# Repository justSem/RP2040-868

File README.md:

> `BE AWARE` This project is still in active development, I'm still in the process of ordering and testing prototypes, so the latest version is not tested to be fully-working as of yet.

# RP2040-868
A GPRS/GNSS/BTLE and LiPo/Li-ion charger integrated Pi Pico on credit-card format.

_Size: 99x50mm_

Title says it all!

This is a fully integrated RP2040-based board featuring the following:

* GPRS Enabled (with microSIM card format)
* GNSS (GPS, GLONASS, BEIDOU)
* BT(LE)
* Integrated LiPo/Li-ion charging circuit.
* USB-C (in USB2.0 mode) ports for future proofing.
* Programmable as if it's a "normal" RPI Pico
* Auto-switching power source: In case you connect both the Battery/USB Power and the USB-Program port, the device will automatically switch it's power source to the "PROG" port.

## The boards origin
Me and my friends work with GPS trackers a lot, for various purposes. For a while we used cheap AliExpress trackers, but we felt they couldn't be fully trusted. They're dirt-cheap but in return, closed-source.
We had absolutely no guarantee that it won't secretly send our data back to China.
So I decided to make our own version.

What started as a simple board grew out to be a fully-programmable board.
Since most of our group favor Python over C++ (simply because we're more used to Python :) ) we went with an RP2040

## Board Details
* The charger is a Monolithic Power [MP2624](https://www.monolithicpower.com/en/mp2624.html) 
* The GPRS/GNSS/BT(LE) Module is a SIMCom [SIM868](https://datasheet.lcsc.com/lcsc/1811011410_SIMCom-Wireless-Solutions-SIM868_C89549.pdf)
* At the heart of the board you'll find a Raspberry Pi [RP2040](https://datasheets.raspberrypi.com/rp2040/rp2040-datasheet.pdf)

## Quick Start
If you have the board you can simply access the programming mode by going through the following steps:
1. Connect a USB-C cable to the port labeled `PROG`
2. Press and hold the `RESET` button
3. Pres and hold the `PROG` button
4. Release the `RESET` button
5. Release the `PROG` button

The device should now present itself as removable storage to your system, allowing you to upload/download files to/from it.
You can use the provided code for some working examples.

## Costs
I haven't exactly calculated the costs. But for the 5 prototypes I built I spent roughly 30 euro's/board.
This includes overhead as some components had a minimium buy of 100 pieces.
So the exact costs are most likely below the number mentioned above.

# Planned Future
The plan is to make some changes in the future, these changes could be:

__Move to another Cellular Chip__

The SimCom chips can have 2A peak currents, which require a pcb designed to accomodate said currents.

__Support for more modern cellular acces__

GPRS is soon to be EOL. But at the time of writing there are no subsitutes which are worth the price in this project.
3G chips are available, but those networks are to be turned off 03-2022 in this country, which makes them not suitable for this project.
LTE-M (or other IoT bands) are still only available to commercial customers, chips for these networks are readily available but sadly not usable in this country.

For now it's waiting to see if any decent substitute will become available in the upcoming months.

__Support NanoSIM__

While it's theoretically possible with Rev 1.1 of the board, it hasn't been tested as of yet.

# F.A.Q.

__Do you sell these boards?__

No. I have no commercial interest with this project, but I might have spares at times, which I might be willing to send as long as you cover the costs.
Feel free to reach out if you're interested.

__Can you implement feature X?__

You're free to implement any software feature yourself. The boards are programmable for a reason :)

The board files can be altered using KiCad, enabling you to make hardware changes as well.

__I found a flaw__

Great! Please open an [issue](/issues/new/choose) and describe what you found.

# DISCLAIMER
I am in no way a professional PCB designer - this design could be flawed without me being aware of it.
I make things as a hobby without any guarantee on functionality, compatibility or reliability.
As stated in the [License](LICENSE.md) this product comes without any guarantee.

# CHANGELOG
### Rev 3.1
* Reversed change in crystal due to availability issues.
* Swapped SOIC-8 Flash for WSON variant.
* Removed SIM from `PROG` power-stage - no suitable DC-DC converter available for a reasonable price to do 5V->4V @ 2A.
* In order to access the SIM868 whilst programming, it is now required to either connect a battery, or an USB-cable to the `CHARGE` power-stage.

### Rev 2.0
* Swapped 100nF caps for 0402 to get them closer to the MCU.
* Moved around power-stage parts for thermal performance.
* Re-implemented USB connections to comply with USB Spec (impedance issues).

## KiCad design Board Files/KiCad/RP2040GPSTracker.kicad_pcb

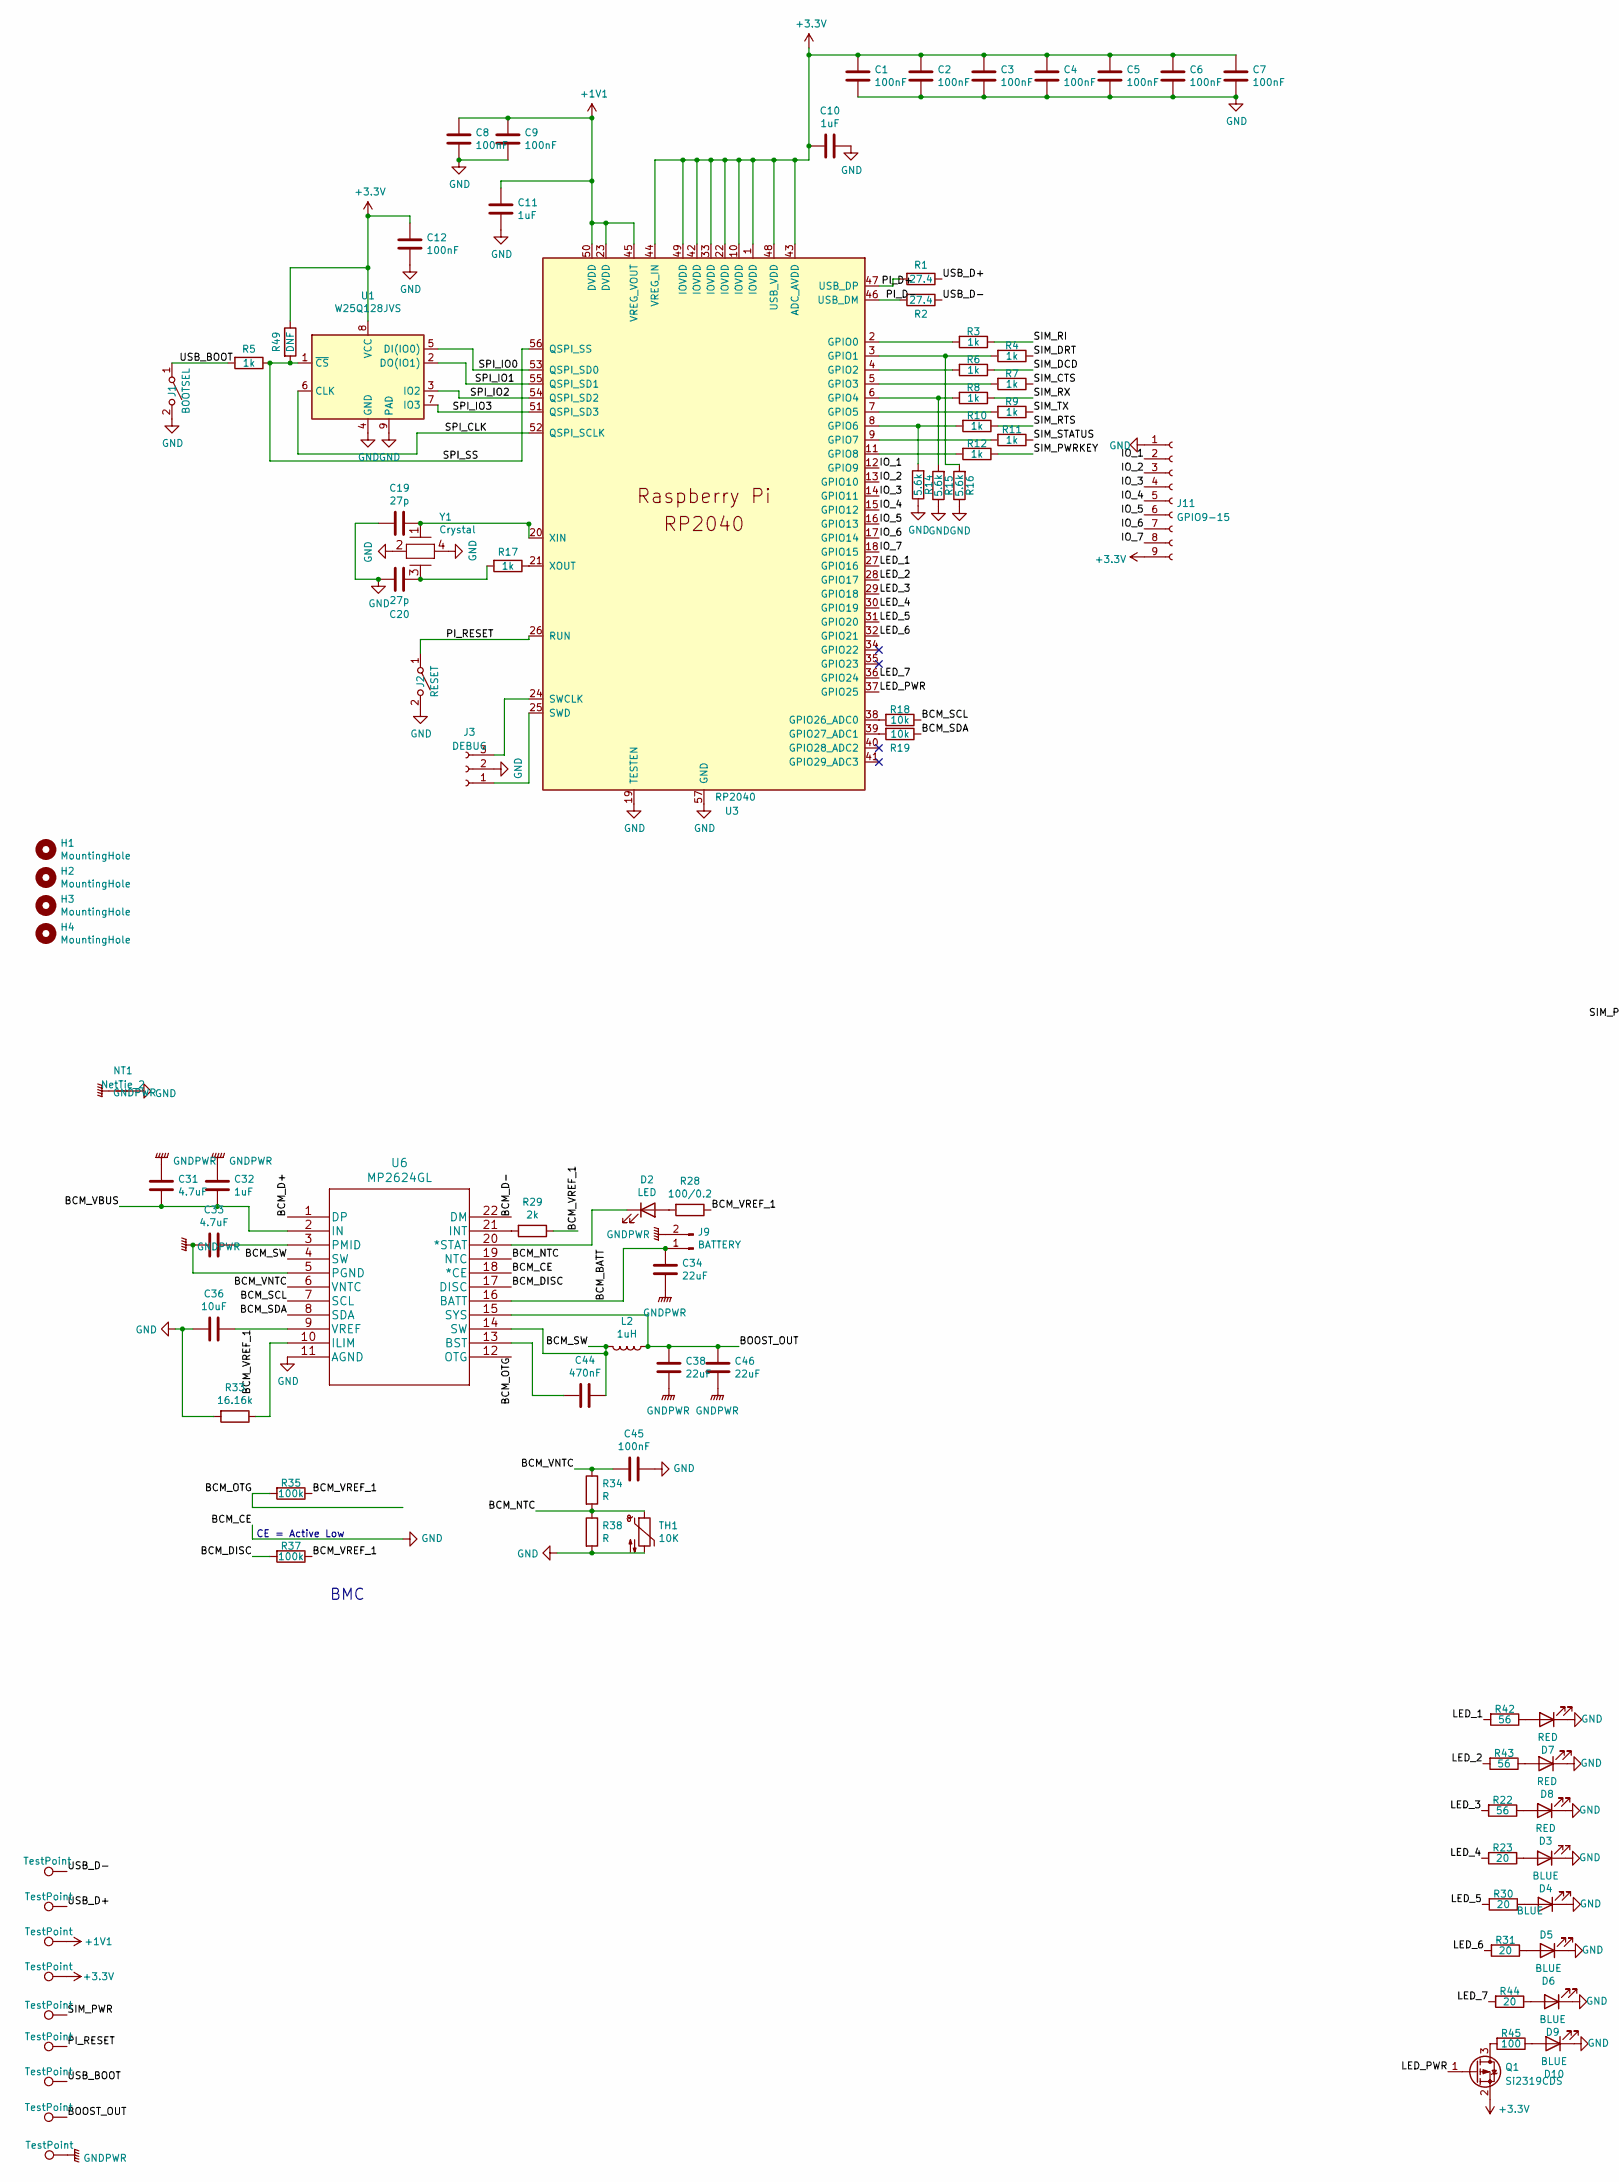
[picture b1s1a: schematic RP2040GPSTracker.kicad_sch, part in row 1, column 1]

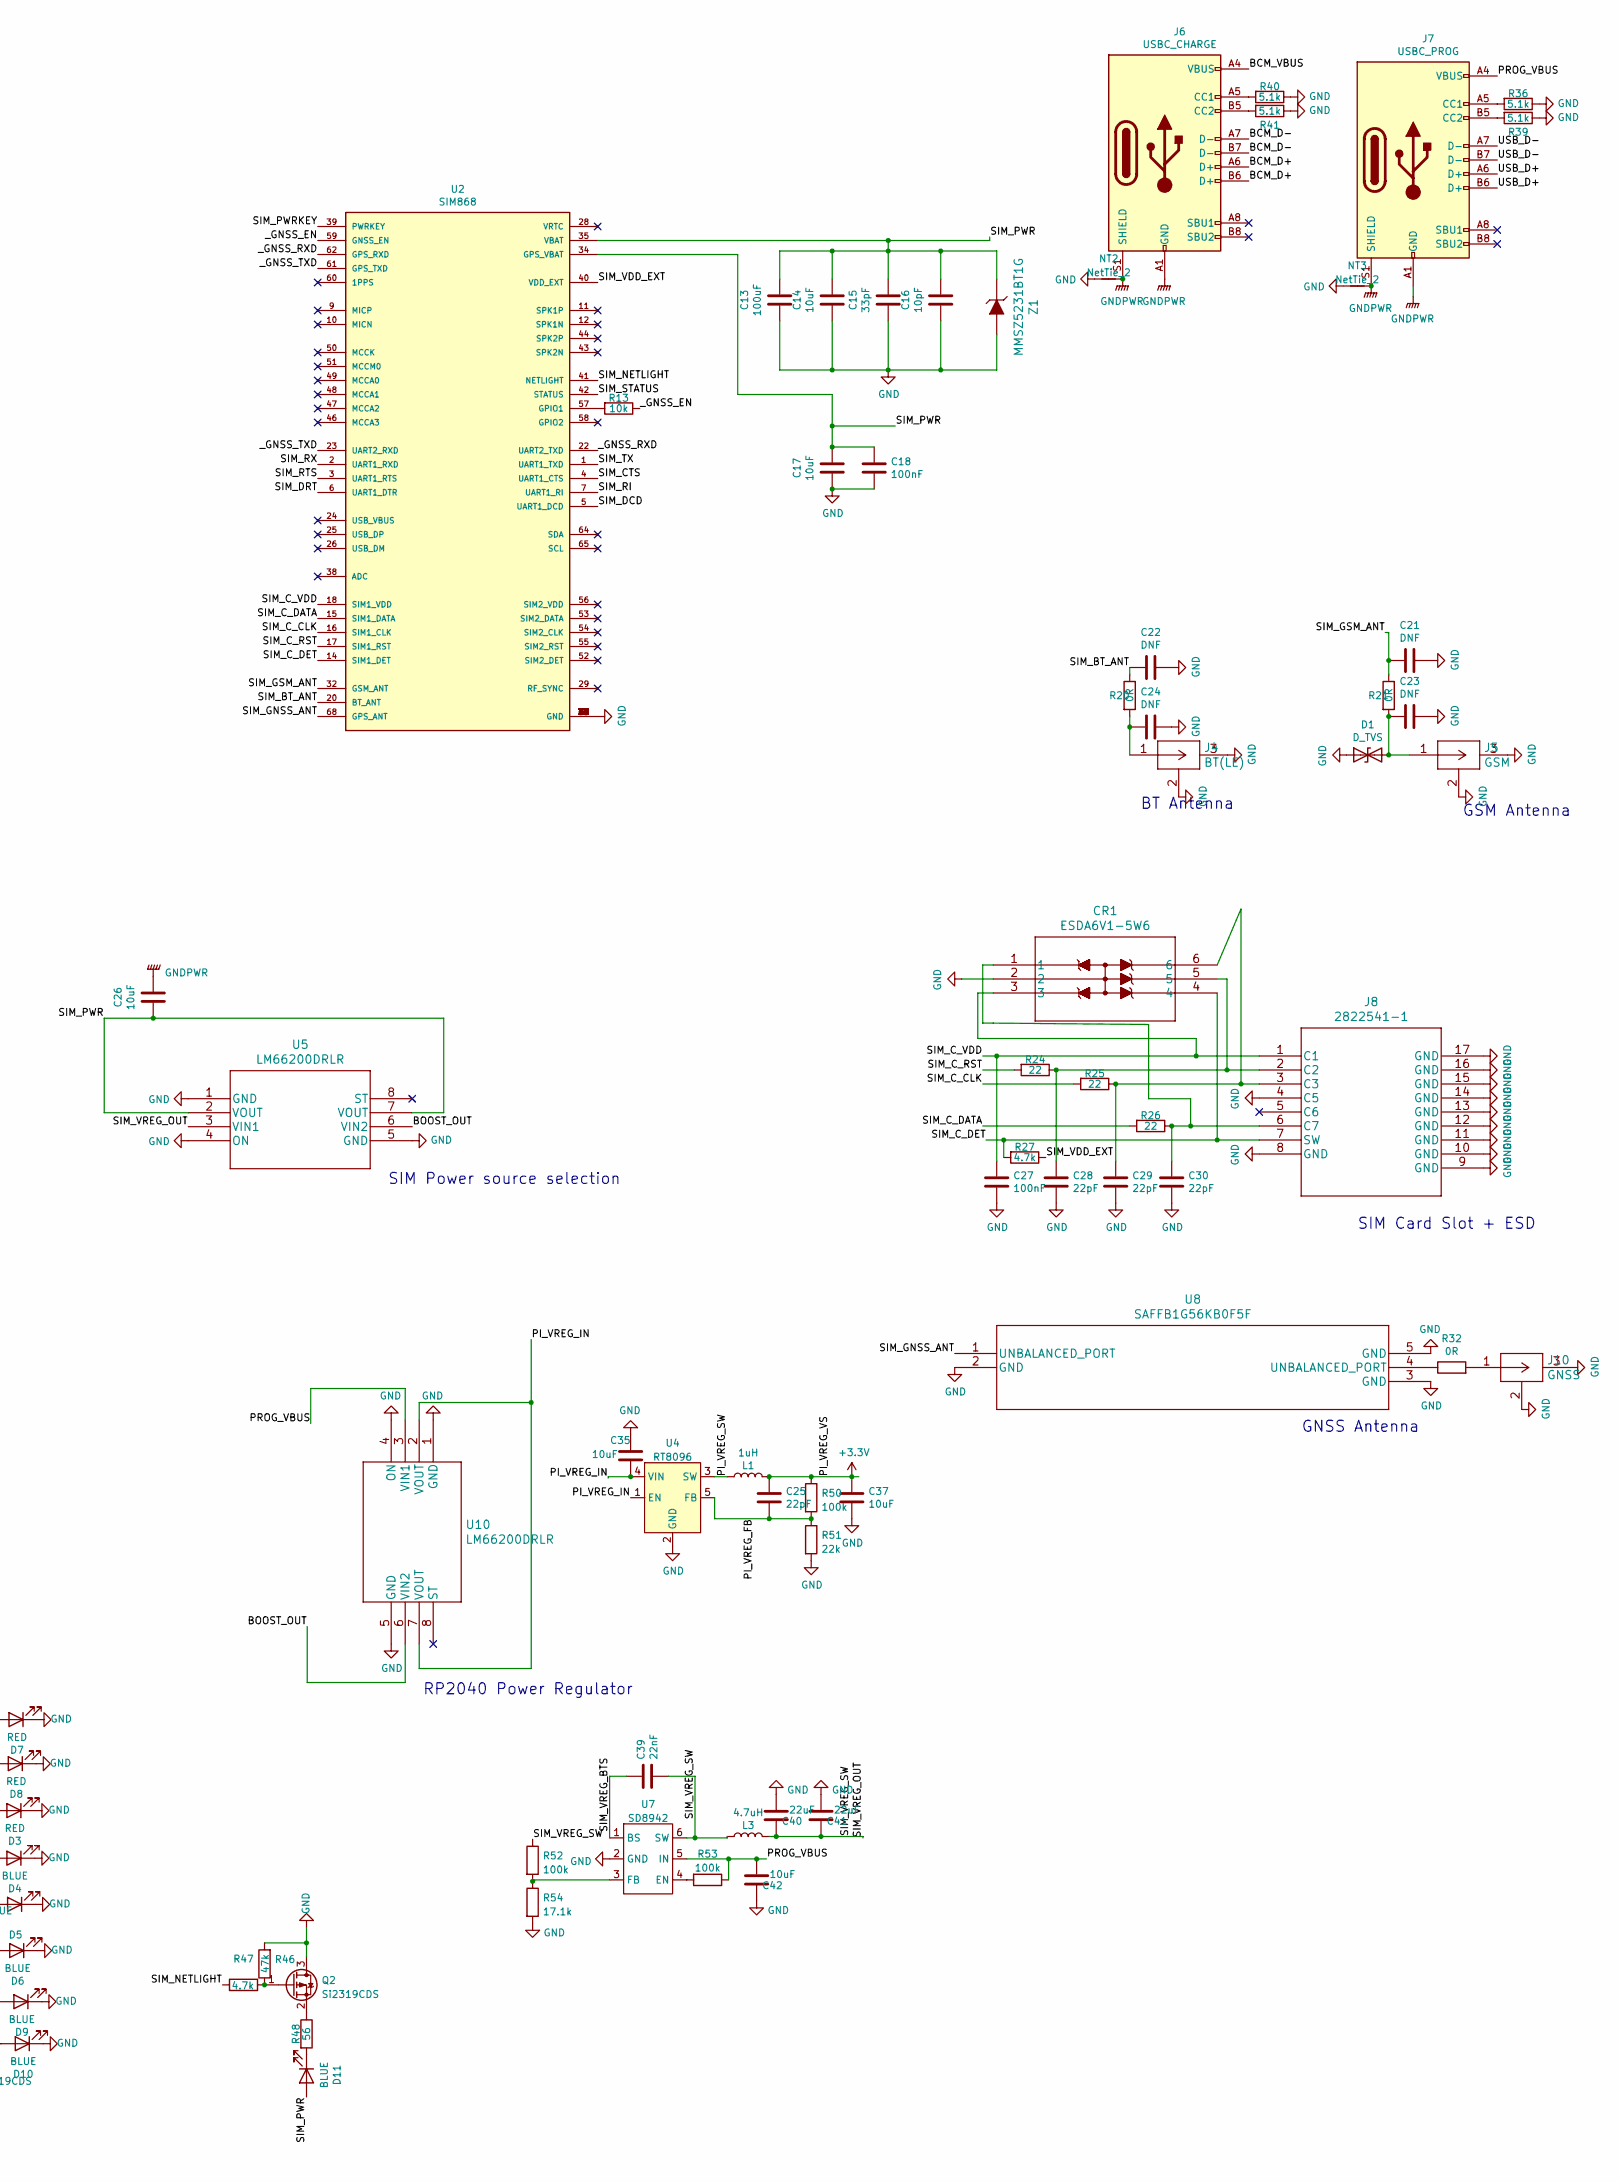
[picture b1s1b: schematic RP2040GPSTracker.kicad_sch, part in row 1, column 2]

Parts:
C1, C2, C3, C4, C5, C6, C7, C8, C9, C12: 100nF; C_0402_1005Metric
C10, C11: 1uF; C_0402_1005Metric
C13: 100uF; CP_EIA-3528-15_AVX-H
C14, C17, C26, C35, C36, C37, C42: 10uF; C_0603_1608Metric
C15: 33pF; C_0603_1608Metric
C16: 10pF; C_0603_1608Metric
C18, C27, C45: 100nF; C_0603_1608Metric
C19, C20: 27p; C_0603_1608Metric
C21, C22, C23, C24: DNF; C_0603_1608Metric
C25, C28, C29, C30: 22pF; C_0603_1608Metric
C31: 4.7uF; C_1206_3216Metric
C32: 1uF; C_0603_1608Metric
C33: 4.7uF; C_0805_2012Metric
C34, C38, C46: 22uF; C_1206_3216Metric
C39: 22nF; C_0603_1608Metric
C40, C41: 22uF; C_0603_1608Metric
C44: 470nF; C_0603_1608Metric
CR1: ESDA6V1-5W6; SOT-363_SC-70-6
D1: D_TVS; D_0603_1608Metric
D2: LED; LED_0805_2012Metric
D3, D7, D8: RED; LED_0805_2012Metric
D4, D5, D6, D9, D10, D11: BLUE; LED_0805_2012Metric
H1, H2, H3, H4: MountingHole; MountingHole_3.2mm_M3_Pad
J1: BOOTSEL; SW_SPST_ALPS_SKRKAEE020
J2: RESET; SW_SPST_ALPS_SKRKAEE020
J3: DEBUG; PinSocket_1x03_P1.27mm_Vertical
J4: BT(LE); U.FL-R-SMT10
J5: GSM; U.FL-R-SMT10
J6: USBC_CHARGE; USB_C_Receptacle_HRO_TYPE-C-31-M-31
J7: USBC_PROG; USB_C_Receptacle_HRO_TYPE-C-31-M-31
J8: 2822541-1
J9: BATTERY; JST_PH_S2B-PH-K_1x02_P2.00mm_Horizontal
J10: GNSS; U.FL-R-SMT10
J11: GPIO9-15; PinHeader_1x09_P2.54mm_Vertical
L1: 1uH; L_1008_2520Metric
L2: 1uH; L_Sumida_CDMC6D28_7.25x6.5mm
L3: 4.7uH; MCS-0530
NT1: NetTie_2; NetTie-2_SMD_Pad2.0mm
NT2, NT3: NetTie_2; NetTie-2_SMD_Pad0.5mm
Q1, Q2: Si2319CDS; SOT-23
R1, R2: 27.4; R_0603_1608Metric
R3, R4, R5, R6, R7, R8, R9, R10, R11, R12, R17: 1k; R_0603_1608Metric
R13, R18, R19: 10k; R_0603_1608Metric
R14, R15, R16: 5.6k; R_0603_1608Metric
R20, R21, R32: 0R; R_0603_1608Metric
R22, R42, R43, R48: 56; R_0603_1608Metric
R23, R30, R31, R44: 20; R_0603_1608Metric
R24, R25, R26: 22; R_0603_1608Metric
R27, R47: 4.7k; R_0603_1608Metric
R28: 100/0.2; R_0603_1608Metric
R29: 2k; R_0603_1608Metric
R33: 16.16k; R_0603_1608Metric
R34, R38: R; R_0603_1608Metric
R35, R37, R50, R52, R53: 100k; R_0603_1608Metric
R36, R39, R40, R41: 5.1k; R_0402_1005Metric
R45: 100; R_0603_1608Metric
R46: 47k; R_0603_1608Metric
R49: DNF; R_0402_1005Metric
R51: 22k; R_0603_1608Metric
R54: 17.1k; R_0603_1608Metric
TH1: 10K; R_0603_1608Metric
TP1, TP2, TP3, TP4, TP5, TP6, TP7, TP8, TP9: TestPoint; TestPoint_Pad_1.5x1.5mm
U1: W25Q128JVS; WSON-8-1EP_6x5mm_P1.27mm_EP3.4x4.3mm
U2: SIM868; XCVR_SIM868
U3: RP2040; RP2040-QFN-56
U4: RT8096; TSOT-23-5
U5, U10: LM66200DRLR
U6: MP2624GL
U7: SD8942; SOT-23-6
U8: SAFFB1G56KB0F5F
Y1: Crystal; ABMM2-12.000MHZ-E2-T
Z1: MMSZ5231BT1G; SOD-123; MPN MMSZ5231BT1G; Digi-Key_PN MMSZ5231B-FDICT-ND

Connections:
+1V1: C8.1, C9.1, C11.1, TP3.1, U3.23 (DVDD), U3.45 (VREG_VOUT), U3.50 (DVDD)
+3V3: C1.2, C2.2, C3.2, C4.2, C5.2, C6.2, C7.2, C10.2, C12.1, C25.1, C37.1, J11.9, L1.2, Q1.2 (S), R49.1, R50.1, TP4.1, U1.8 (VCC), U3.1 (IOVDD), U3.10 (IOVDD), U3.22 (IOVDD), U3.33 (IOVDD), U3.42 (IOVDD), U3.43 (ADC_AVDD), U3.44 (VREG_IN), U3.48 (USB_VDD), U3.49 (IOVDD)
/BCM_BATT: C34.1, J9.1, U6.16 (BATT)
/BCM_D+: J6.A6 (D+), J6.B6 (D+), U6.1 (DP)
/BCM_D-: J6.A7 (D-), J6.B7 (D-), U6.22 (DM)
/BCM_DISC: R37.2, U6.17 (DISC)
/BCM_NTC: R34.2, R38.1, TH1.1, U6.19 (NTC)
/BCM_OTG: R35.2, U6.12 (OTG)
/BCM_SCL: R18.1, U6.7 (SCL)
/BCM_SDA: R19.1, U6.8 (SDA)
/BCM_SW: C44.1, L2.2, U6.4 (SW), U6.14 (SW)
/BCM_VBUS: C31.2, C32.2, J6.A4 (VBUS), J6.A9 (VBUS), J6.B4 (VBUS), J6.B9 (VBUS), U6.2 (IN)
/BCM_VNTC: C45.1, R34.1, U6.6 (VNTC)
/BCM_VREF_1: C36.1, R28.1, R29.1, R35.1, R37.1, U6.9 (VREF)
/IO_1: J11.2, U3.12 (GPIO9)
/IO_2: J11.3, U3.13 (GPIO10)
/IO_3: J11.4, U3.14 (GPIO11)
/IO_4: J11.5, U3.15 (GPIO12)
/IO_5: J11.6, U3.16 (GPIO13)
/IO_6: J11.7, U3.17 (GPIO14)
/IO_7: J11.8, U3.18 (GPIO15)
/LED_1: R42.2, U3.27 (GPIO16)
/LED_2: R43.2, U3.28 (GPIO17)
/LED_3: R22.2, U3.29 (GPIO18)
/LED_4: R23.2, U3.30 (GPIO19)
/LED_5: R30.2, U3.31 (GPIO20)
/LED_6: R31.2, U3.32 (GPIO21)
/LED_7: R44.2, U3.36 (GPIO24)
/LED_PWR: Q1.1 (G), U3.37 (GPIO25)
/PI_D+: R1.2, U3.47 (USB_DP)
/PI_D-: R2.2, U3.46 (USB_DM)
/PI_RESET: J2.1 (A), TP6.1, U3.26 (RUN)
/PI_VREG_FB: C25.2, R50.2, R51.1, U4.5 (FB)
/PI_VREG_IN: C35.2, U4.1 (EN), U4.4 (VIN), U10.2 (VOUT), U10.7 (VOUT)
/PI_VREG_SW: L1.1, U4.3 (SW)
/PROG_VBUS: C42.2, J7.A4 (VBUS), J7.A9 (VBUS), J7.B4 (VBUS), J7.B9 (VBUS), R53.1, U7.5 (IN), U10.3 (VIN1)
/SIM_BT_ANT: C22.2, R20.1, U2.20 (BT_ANT)
/SIM_CTS: R7.1, U2.4 (UART1_CTS)
/SIM_C_CLK: R25.2, U2.16 (SIM1_CLK)
/SIM_C_DATA: R26.2, U2.15 (SIM1_DATA)
/SIM_C_DET: CR1.4, J8.7 (SW), R27.2, U2.14 (SIM1_DET)
/SIM_C_RST: R24.2, U2.17 (SIM1_RST)
/SIM_C_VDD: C27.2, CR1.3, J8.1 (C1), U2.18 (SIM1_VDD)
/SIM_DCD: R6.1, U2.5 (UART1_DCD)
/SIM_DRT: R4.1, U2.6 (UART1_DTR)
/SIM_GNSS_ANT: U2.68 (GPS_ANT), U8.1 (UNBALANCED_PORT)
/SIM_GSM_ANT: C21.2, R21.1, U2.32 (GSM_ANT)
/SIM_NETLIGHT: R47.1, U2.41 (NETLIGHT)
/SIM_PWRKEY: R12.1, U2.39 (PWRKEY)
/SIM_RI: R3.1, U2.7 (UART1_RI)
/SIM_RTS: R10.1, U2.3 (UART1_RTS)
/SIM_RX: R8.1, U2.2 (UART1_RXD)
/SIM_STATUS: R11.1, U2.42 (STATUS)
/SIM_TX: R9.1, U2.1 (UART1_TXD)
/SIM_VDD_EXT: R27.1, U2.40 (VDD_EXT)
/SPI_CLK: U1.6 (CLK), U3.52 (QSPI_SCLK)
/SPI_IO0: U1.5 (DI(IO0)), U3.53 (QSPI_SD0)
/SPI_IO1: U1.2 (DO(IO1)), U3.55 (QSPI_SD1)
/SPI_IO2: U1.3 (IO2), U3.54 (QSPI_SD2)
/SPI_IO3: U1.7 (IO3), U3.51 (QSPI_SD3)
/SPI_SS: R5.1, R49.2, U1.1 (~CS), U3.56 (QSPI_SS)
/USB_BOOT: J1.1 (A), R5.2, TP7.1
/USB_D+: J7.A6 (D+), J7.B6 (D+), R1.1, TP2.1
/USB_D-: J7.A7 (D-), J7.B7 (D-), R2.1, TP1.1
/_GNSS_EN: R13.1, U2.59 (GNSS_EN)
/_GNSS_RXD: U2.22 (UART2_TXD), U2.62 (GPS_RXD)
/_GNSS_TXD: U2.23 (UART2_RXD), U2.61 (GPS_TXD)
GNDPWR: C26.1, C31.1, C32.1, C33.2, C34.2, C38.2, C46.2, J6.A1 (GND), J6.A12 (GND), J6.B1 (GND), J6.B12 (GND), J6.S1 (SHIELD), J7.A1 (GND), J7.A12 (GND), J7.B1 (GND), J7.B12 (GND), J7.S1 (SHIELD), J9.2, NT1.1, NT2.2, NT3.2, TP9.1, U6.5 (PGND)
unnamed: C19.1, U3.20 (XIN), Y1.1
unnamed: C23.2, D1.2 (A2), J5.1, R21.2
unnamed: C24.2, J4.1, R20.2
unnamed: C28.2, CR1.5, J8.2 (C2), R24.1
unnamed: C29.2, CR1.6, J8.3 (C3), R25.1
unnamed: C30.2, CR1.1, J8.6 (C7), R26.1
unnamed: C33.1, U6.3 (PMID)
unnamed: C39.1, U7.1 (BS)
unnamed: C39.2, C40.1, C41.1, L3.1, L3.2, R52.1, U5.3 (VIN1), U7.6 (SW)
unnamed: C44.2, U6.13 (BST)
unnamed: D2.1 (K), U6.20 (*STAT)
unnamed: D2.2 (A), R28.2
unnamed: D3.2 (A), R22.1
unnamed: D4.2 (A), R23.1
unnamed: D5.2 (A), R30.1
unnamed: D6.2 (A), R31.1
unnamed: D7.2 (A), R42.1
unnamed: D8.2 (A), R43.1
unnamed: D9.2 (A), R44.1
unnamed: D10.2 (A), R45.1
unnamed: D11.1 (K), R48.2
unnamed: J3.1, U3.25 (SWD)
unnamed: J3.3, U3.24 (SWCLK)
unnamed: J6.A5 (CC1), R40.2
unnamed: J6.B5 (CC2), R41.2
unnamed: J7.A5 (CC1), R36.2
unnamed: J7.B5 (CC2), R39.2
unnamed: J10.1, R32.2
unnamed: Q1.3 (D), R45.2
unnamed: Q2.1 (G), R46.1, R47.2
unnamed: Q2.2 (S), R48.1
unnamed: R3.2, U3.2 (GPIO0)
unnamed: R6.2, U3.4 (GPIO2)
unnamed: R7.2, U3.5 (GPIO3)
unnamed: R9.2, U3.7 (GPIO5)
unnamed: R10.2, R14.2, U3.8 (GPIO6)
unnamed: R11.2, U3.9 (GPIO7)
unnamed: R12.2, U3.11 (GPIO8)
unnamed: R13.2, U2.57 (GPIO1)
unnamed: R8.2, R15.2, U3.6 (GPIO4)
unnamed: R4.2, R16.2, U3.3 (GPIO1)
unnamed: R17.1, U3.21 (XOUT)
unnamed: R18.2, U3.38 (GPIO26_ADC0)
unnamed: R19.2, U3.39 (GPIO27_ADC1)
unnamed: R29.2, U6.21 (INT)
unnamed: R32.1, U8.4 (UNBALANCED_PORT)
unnamed: R33.1, U6.10 (ILIM)
unnamed: R52.2, R54.1, U7.3 (FB)
unnamed: R53.2, U7.4 (EN)

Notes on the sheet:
SIM Card Slot + ESD
RP2040 Power Regulator
SIM Power source selection
BMC
GNSS Antenna
BT Antenna
GSM Antenna
CE = Active Low

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
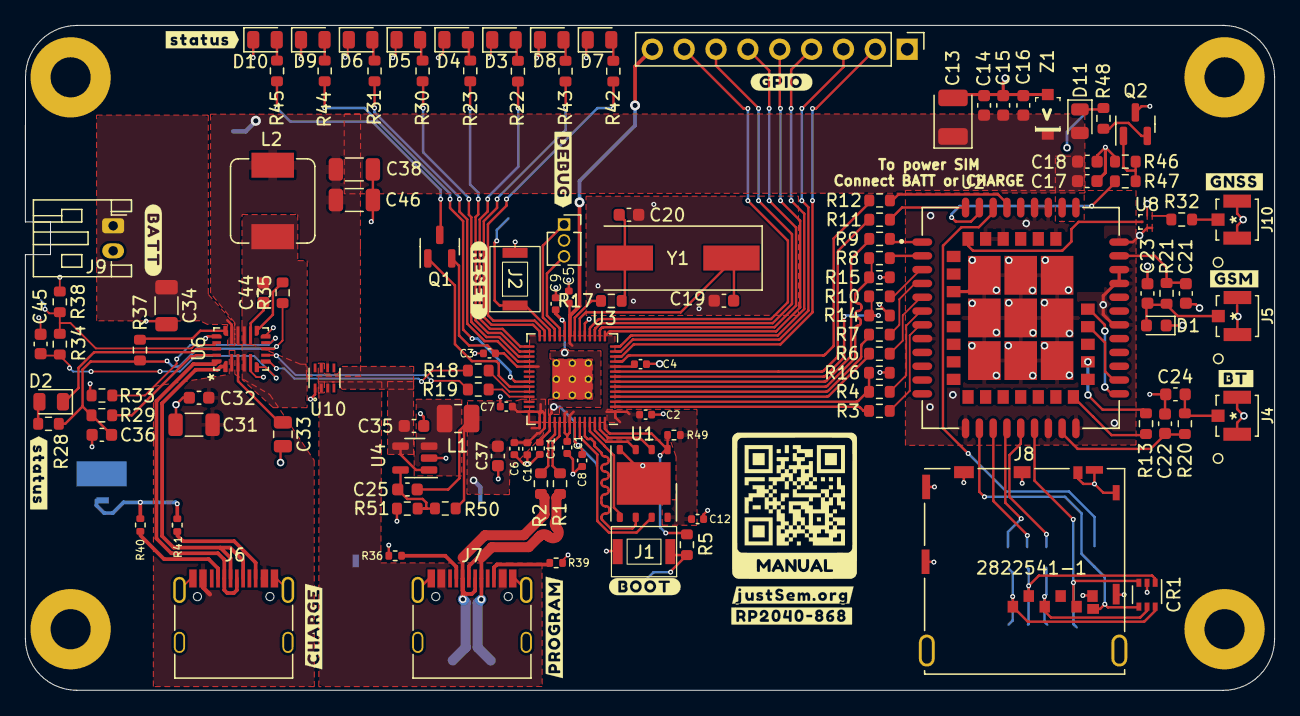
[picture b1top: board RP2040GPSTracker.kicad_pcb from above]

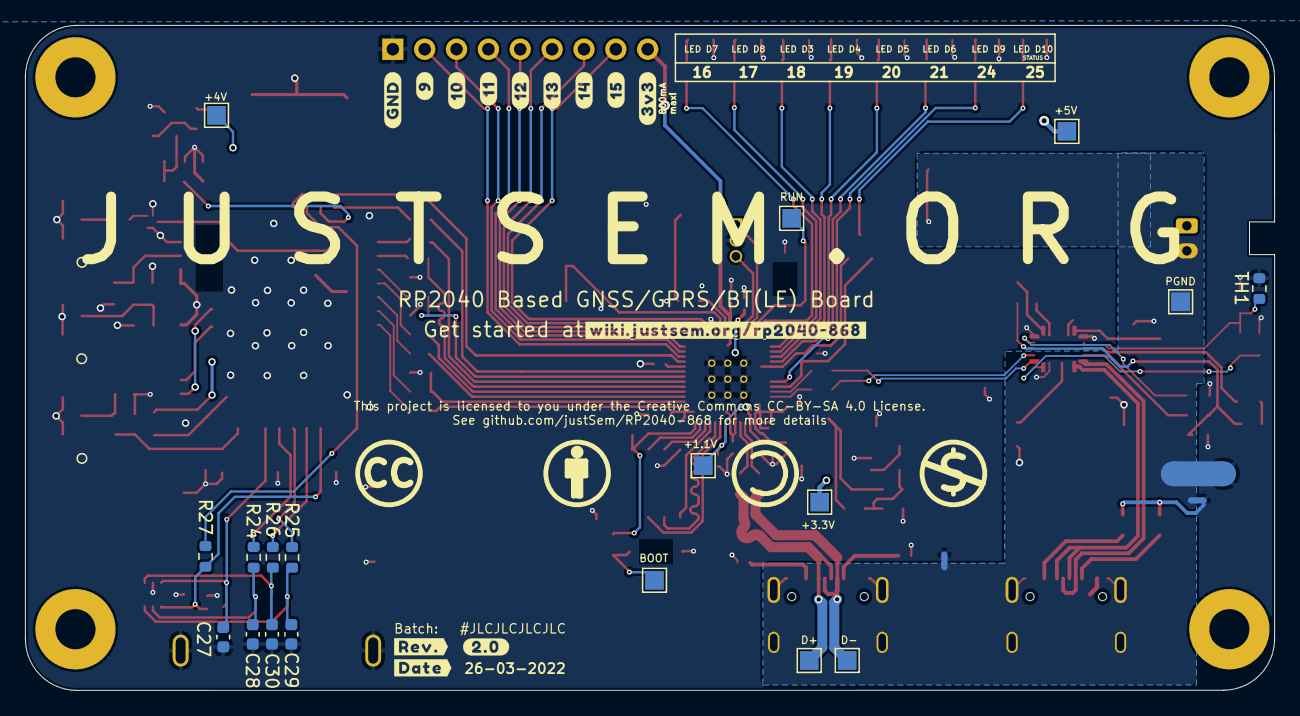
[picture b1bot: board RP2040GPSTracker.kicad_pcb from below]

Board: 2 copper layers, 99.6 x 53.0 mm, 144 parts (21 on the bottom side), 116 nets.

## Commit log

2022-03-01 Board Rev 1.1
2022-03-01 README Update
2022-03-01 better images
2022-03-01 Documentation
2022-03-01 Deleted obsoletes
2022-03-01 Readme and Documentation
2022-03-01 Added warning
2022-03-01 Updated type in Board Files
2022-03-03 Added 3D case
2022-03-04 Updated Case clearances and wall widths
2022-03-08 Updated USB trace differential routing
2022-03-08 Removed macOS Junk
2022-03-15 Documentation Move
2022-03-15 Board optimizations
2022-03-16 Rev 1.2, Swapped out C13 Footprint for more suitable one
2022-03-17 Added board schematic
2022-03-18 Rev 1.3. Implemented USB-C CC Channels. Fixed Z1 rotation. Expanded GPIO
2022-03-18 Updated images
2022-03-26 Rev 2.0
2022-03-29 Rev 3.1 - Power-stage overhaul, SIM power finetuning
2022-03-29 Changelog
2022-03-30 Revised case to accomodate new board layout

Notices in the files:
Board Files/KiCad/RP2040GPSTracker.kicad_pcb:
This project is licensed to you under the Creative Commons CC-BY-SA 4.0 License.
parts and their libraries:
Copyright 2021 Accelerated Designs. All rights reserved.
